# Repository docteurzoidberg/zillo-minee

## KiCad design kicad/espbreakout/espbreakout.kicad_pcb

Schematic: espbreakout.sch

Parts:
D1: POWER; LED_1206_3216Metric_Pad1.42x1.75mm_HandSolder
D2: RELAY; LED_1206_3216Metric_Pad1.42x1.75mm_HandSolder
H1, H2, H3, H4: MountingHole_Pad; MountingHole_3.2mm_M3_Pad_Via
J1: TEMPERATURE; PhoenixContact_MCV-G_03x3.81mm_Vertical
J2: LED DATA; PhoenixContact_MCV-G_03x3.81mm_Vertical
J3: UNK; PhoenixContact_MCV-G_03x3.81mm_Vertical
J4: POWER; PhoenixContact_MCV-G_03x3.81mm_Vertical
J5: CURRENT; PhoenixContact_MCV-G_03x3.81mm_Vertical
J6: RELAY; PhoenixContact_MCV-G_03x3.81mm_Vertical
J7: GROVE_I2C; JST_PH_S5B-PH-K_05x2.00mm_Angled
J8: SERIAL; Pin_Header_Straight_1x05_Pitch2.54mm
JP1, JP2: PLJP; SolderJumper-2_P1.3mm_Open_RoundedPad1.0x1.5mm
JP3, JP5, JP14: SolderJumper_2_Open; SolderJumper-2_P1.3mm_Open_TrianglePad1.0x1.5mm
JP4, JP6, JP7: D; SolderJumper-2_P1.3mm_Open_TrianglePad1.0x1.5mm
JP8, JP9, JP10, JP11, JP12, JP13: Jumper_3_Open; SolderJumper-3_P1.3mm_Open_Pad1.0x1.5mm
R1, R2: 4.7K; R_0805_HandSoldering
R3: 150; R_0805_HandSoldering
R4: 51; R_0805_HandSoldering
U1: ESP32-38pins; esp32 38pin azdelivery

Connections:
3V3: J7.3, J8.1, JP8.3, JP9.3, JP10.3, JP11.3, JP12.3, JP13.3, R1.1, R2.1, U1.1
5V: J7.1, JP1.2 (B), JP8.1, JP9.1, JP10.1, JP11.1, JP12.1, JP13.1, U1.19
CURRENT_SENSOR: JP6.1 (A)
GND: D1.1 (K), D2.1 (K), H1.1, H2.1, H3.1, H4.1, J1.3, J2.3, J3.3, J4.3, J5.3, J6.3, J7.2, J8.5, U1.14, U1.20, U1.26
GPIO0: J8.4, U1.33
LEDMATRIX: U1.9
LED_DATA: JP5.2 (B)
unnamed: D1.2 (A), R3.2
unnamed: D2.2 (A), R4.2
unnamed: J1.1, JP8.2
unnamed: J1.2, JP3.1 (A)
unnamed: J2.1, JP11.2
unnamed: J2.2, JP5.1 (A)
unnamed: J3.1, JP13.2
unnamed: J3.2, JP14.1 (A)
unnamed: J4.1, JP9.2
unnamed: J4.2, JP4.2 (B)
unnamed: J5.1, JP10.2
unnamed: J5.2, JP6.2 (B)
unnamed: J6.1, JP12.2
unnamed: J6.2, JP7.2 (B)
unnamed: JP1.1 (A), R3.1
unnamed: JP2.1 (A), R4.1
RELAY_TRIGGER: JP2.2 (B), JP7.1 (A)
RX: J8.3
SCL: J7.5, R2.2, U1.22
SDA: J7.4, R1.2, U1.25
TEMP_SENSOR: JP3.2 (B)
TX: J8.2

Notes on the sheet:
LED SIDE
POWER SIDE
PULLUPS
POWER NETS
LEDS

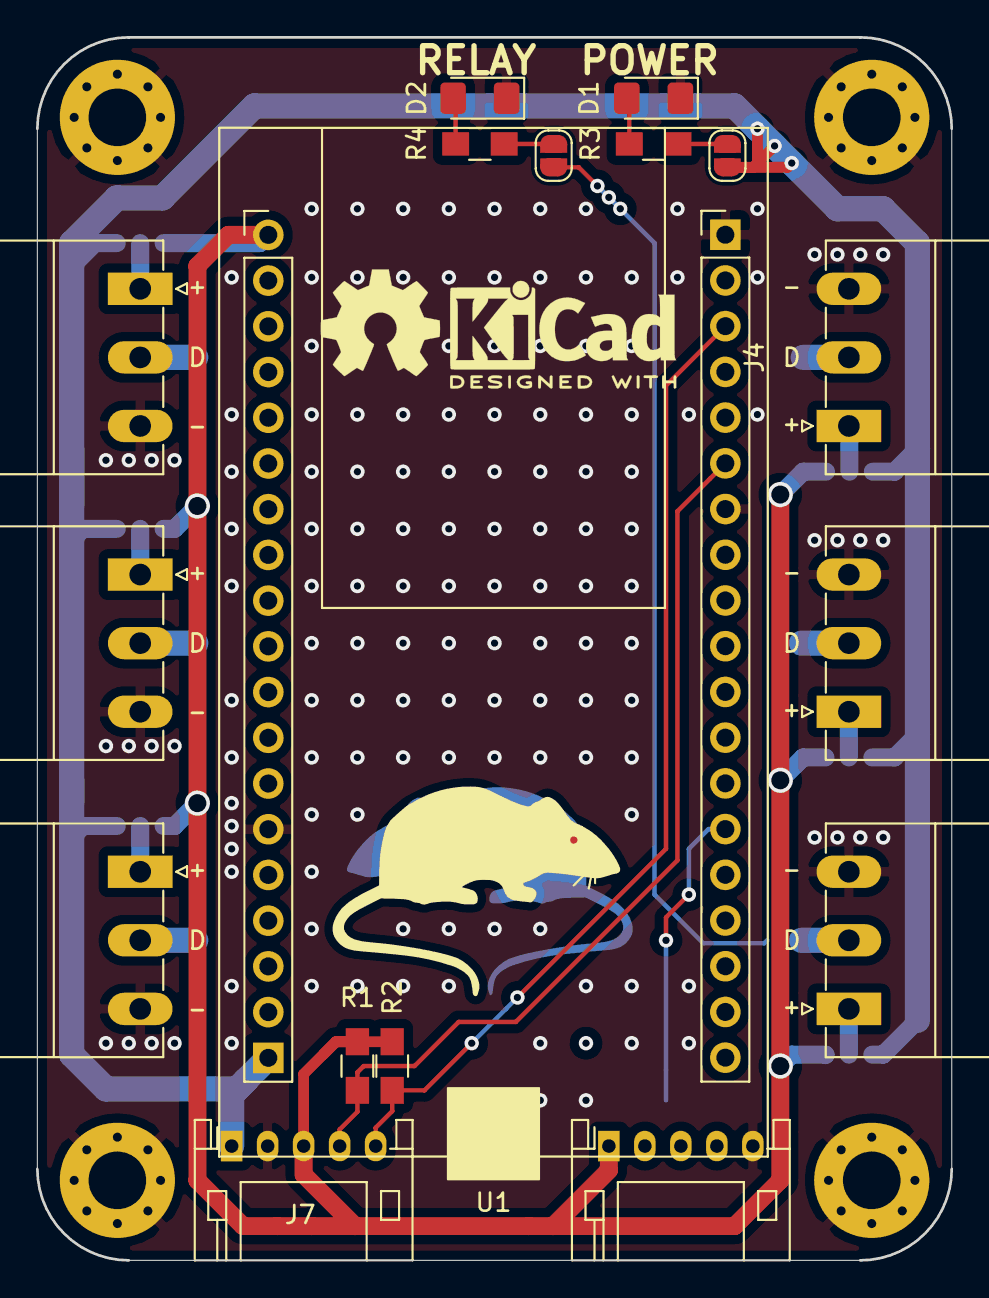
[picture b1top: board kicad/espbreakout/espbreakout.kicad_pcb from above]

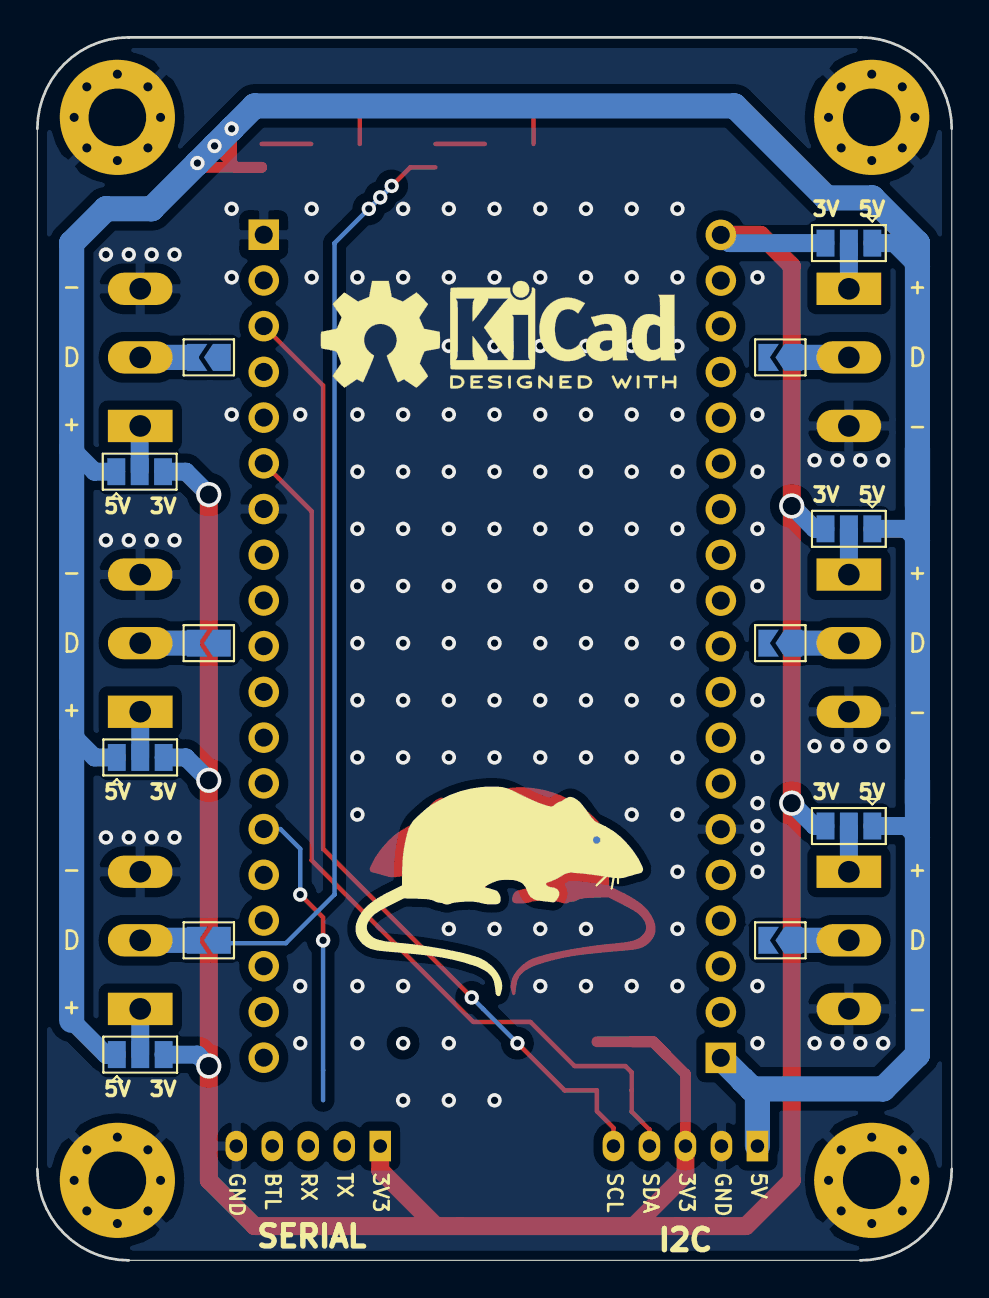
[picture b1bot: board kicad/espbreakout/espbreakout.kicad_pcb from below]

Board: 2 copper layers, 50.8 x 67.9 mm, 33 parts (12 on the bottom side), 23 nets.

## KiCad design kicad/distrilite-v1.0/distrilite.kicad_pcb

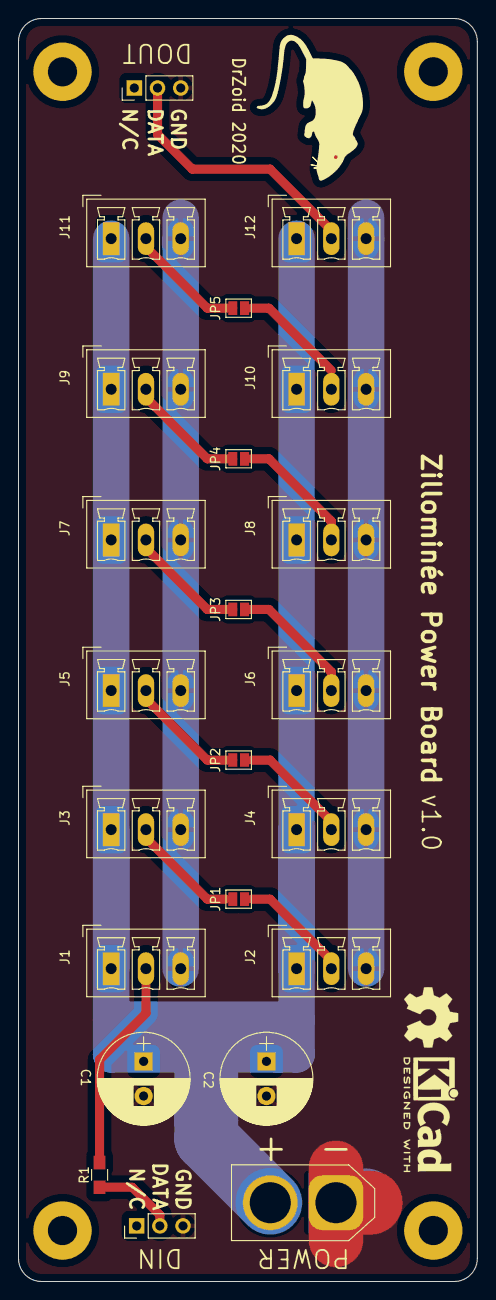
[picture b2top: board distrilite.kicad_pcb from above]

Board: 2 copper layers, 50.3 x 138.4 mm, 27 parts (0 on the bottom side), 15 nets.

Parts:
C1, C2: CP; CP_Radial_D10.0mm_P3.80mm
H1, H2, H3, H4: MountingHole; MountingHole_3.2mm_M3_Pad
J1, J2, J3, J4, J5, J6, J7, J8, J9, J10, J11, J12: Conn_01x03_Male; PhoenixContact_MCV-G_03x3.81mm_Vertical
J13: LED_DOUT; Pin_Header_Straight_1x03_Pitch2.54mm
J34: LED_DIN; Pin_Header_Straight_1x03_Pitch2.54mm
JP1, JP2, JP3, JP4, JP5: SolderJumper_2_Open; SolderJumper-2_P1.3mm_Open_Pad1.0x1.5mm
POWER1: XT60; AMASS_XT60-F_1x02_P7.20mm_Vertical
R1: 470; R_0805_HandSoldering

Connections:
+12V: C1.1, C2.1, J1.1, J2.1, J3.1, J4.1, J5.1, J6.1, J7.1, J8.1, J9.1, J10.1, J11.1, J12.1, POWER1.2
DATA_IN: J1.2, R1.2
DATA_OUT: J12.2, J13.2
GND: C1.2, C2.2, J1.3, J2.3, J3.3, J4.3, J5.3, J6.3, J7.3, J8.3, J9.3, J10.3, J11.3, J12.3, J13.3, J34.3, POWER1.1
unnamed: J2.2, JP1.1
unnamed: J3.2, JP1.2
unnamed: J4.2, JP2.1
unnamed: J5.2, JP2.2
unnamed: J6.2, JP3.1
unnamed: J7.2, JP3.2
unnamed: J8.2, JP4.1
unnamed: J9.2, JP4.2
unnamed: J10.2, JP5.1
unnamed: J11.2, JP5.2
unnamed: J34.2, R1.1

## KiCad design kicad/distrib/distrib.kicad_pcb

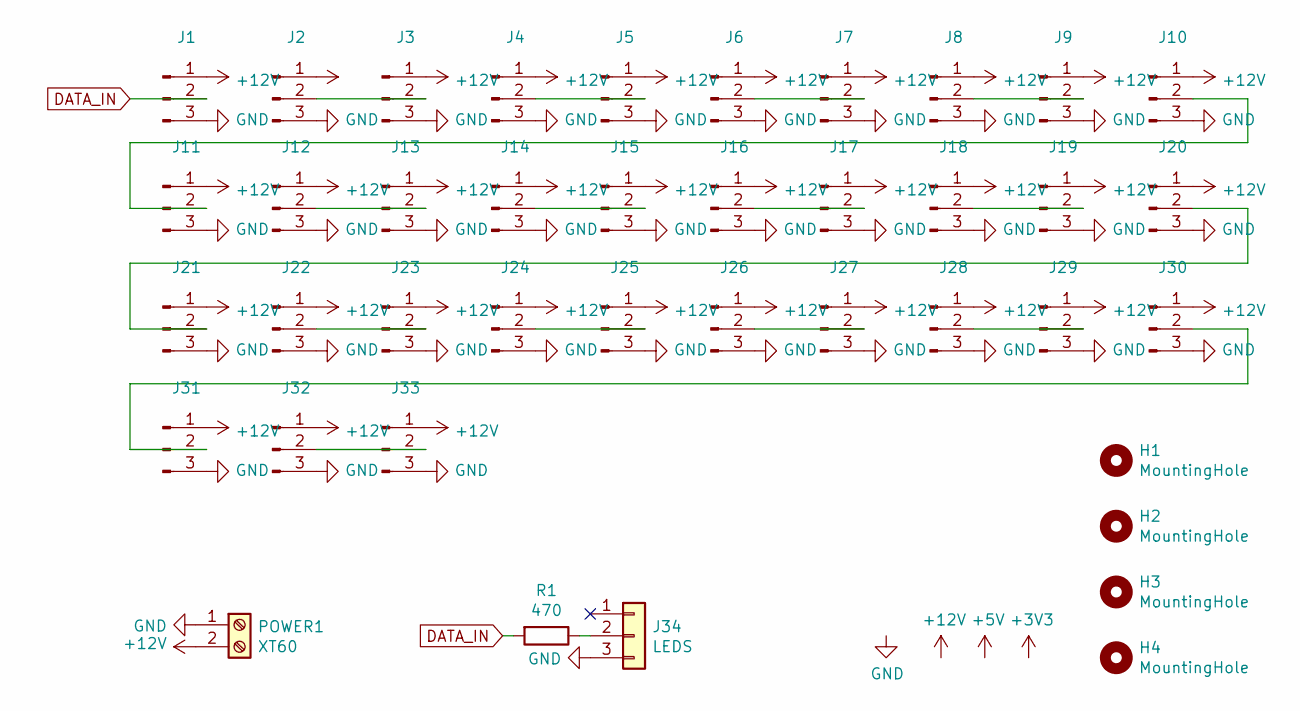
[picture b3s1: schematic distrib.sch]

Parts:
H1, H2, H3, H4: MountingHole; MountingHole_3.2mm_M3
J1, J2, J3, J4, J5, J6, J7, J8, J9, J10, J11, J12, J13, J14, J15, J16, J17, J18, J19, J20, J21, J22, J23, J24, J25, J26, J27, J28, J29, J30, J31, J32, J33: Conn_01x03_Male; PhoenixContact_MCV-G_03x3.81mm_Vertical
J34: LEDS; Pin_Header_Straight_1x03_Pitch2.54mm
POWER1: XT60; AMASS_XT60-F_1x02_P7.20mm_Vertical
R1: 470; R_0805_HandSoldering

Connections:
+12V: J1.1, J2.1, J3.1, J4.1, J5.1, J6.1, J7.1, J8.1, J9.1, J10.1, J11.1, J12.1, J13.1, J14.1, J15.1, J16.1, J17.1, J18.1, J19.1, J20.1, J21.1, J22.1, J23.1, J24.1, J25.1, J26.1, J27.1, J28.1, J29.1, J30.1, J31.1, J32.1, J33.1, POWER1.2; also elsewhere on the board
DATA_IN: J1.2, R1.2
GND: J1.3, J2.3, J3.3, J4.3, J5.3, J6.3, J7.3, J8.3, J9.3, J10.3, J11.3, J12.3, J13.3, J14.3, J15.3, J16.3, J17.3, J18.3, J19.3, J20.3, J21.3, J22.3, J23.3, J24.3, J25.3, J26.3, J27.3, J28.3, J29.3, J30.3, J31.3, J32.3, J33.3, J34.3, POWER1.1; also elsewhere on the board
unnamed: J2.2, J3.2
unnamed: J4.2, J5.2
unnamed: J6.2, J7.2
unnamed: J8.2, J9.2
unnamed: J10.2, J11.2
unnamed: J12.2, J13.2
unnamed: J14.2, J15.2
unnamed: J16.2, J17.2
unnamed: J18.2, J19.2
unnamed: J20.2, J21.2
unnamed: J22.2, J23.2
unnamed: J24.2, J25.2
unnamed: J26.2, J27.2
unnamed: J28.2, J29.2
unnamed: J30.2, J31.2
unnamed: J32.2, J33.2
unnamed: J34.2, R1.1

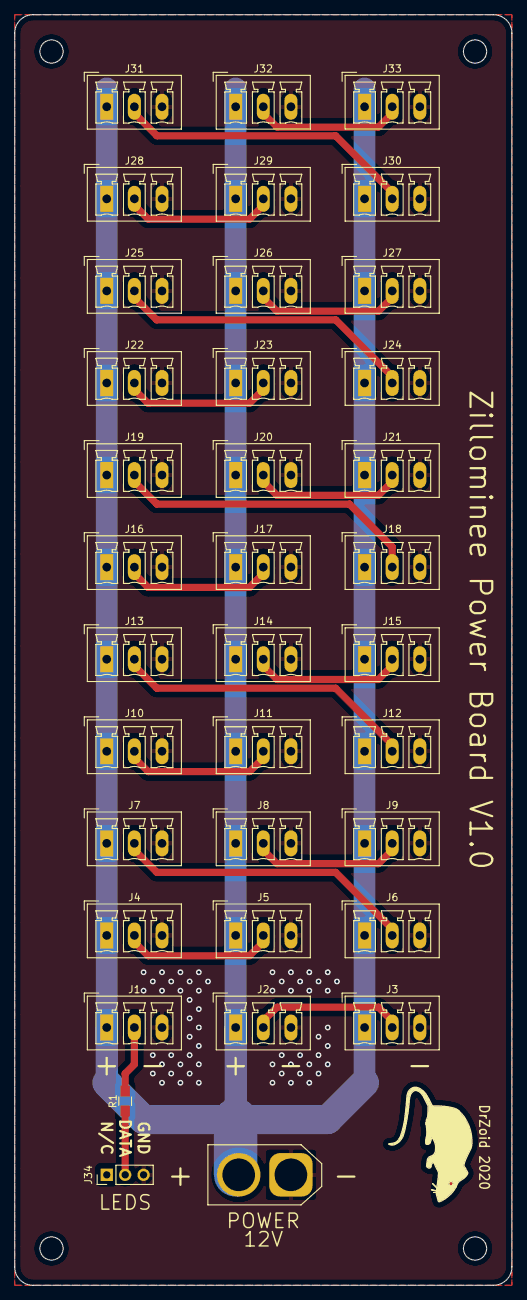
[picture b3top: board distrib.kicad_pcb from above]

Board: 2 copper layers, 68.6 x 175.3 mm, 40 parts (0 on the bottom side), 20 nets.

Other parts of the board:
POWER: XT60; AMASS_XT60-F_1x02_P7.20mm_Vertical

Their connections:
+12V: POWER.2; also elsewhere on the board
GND: POWER.1; also elsewhere on the board

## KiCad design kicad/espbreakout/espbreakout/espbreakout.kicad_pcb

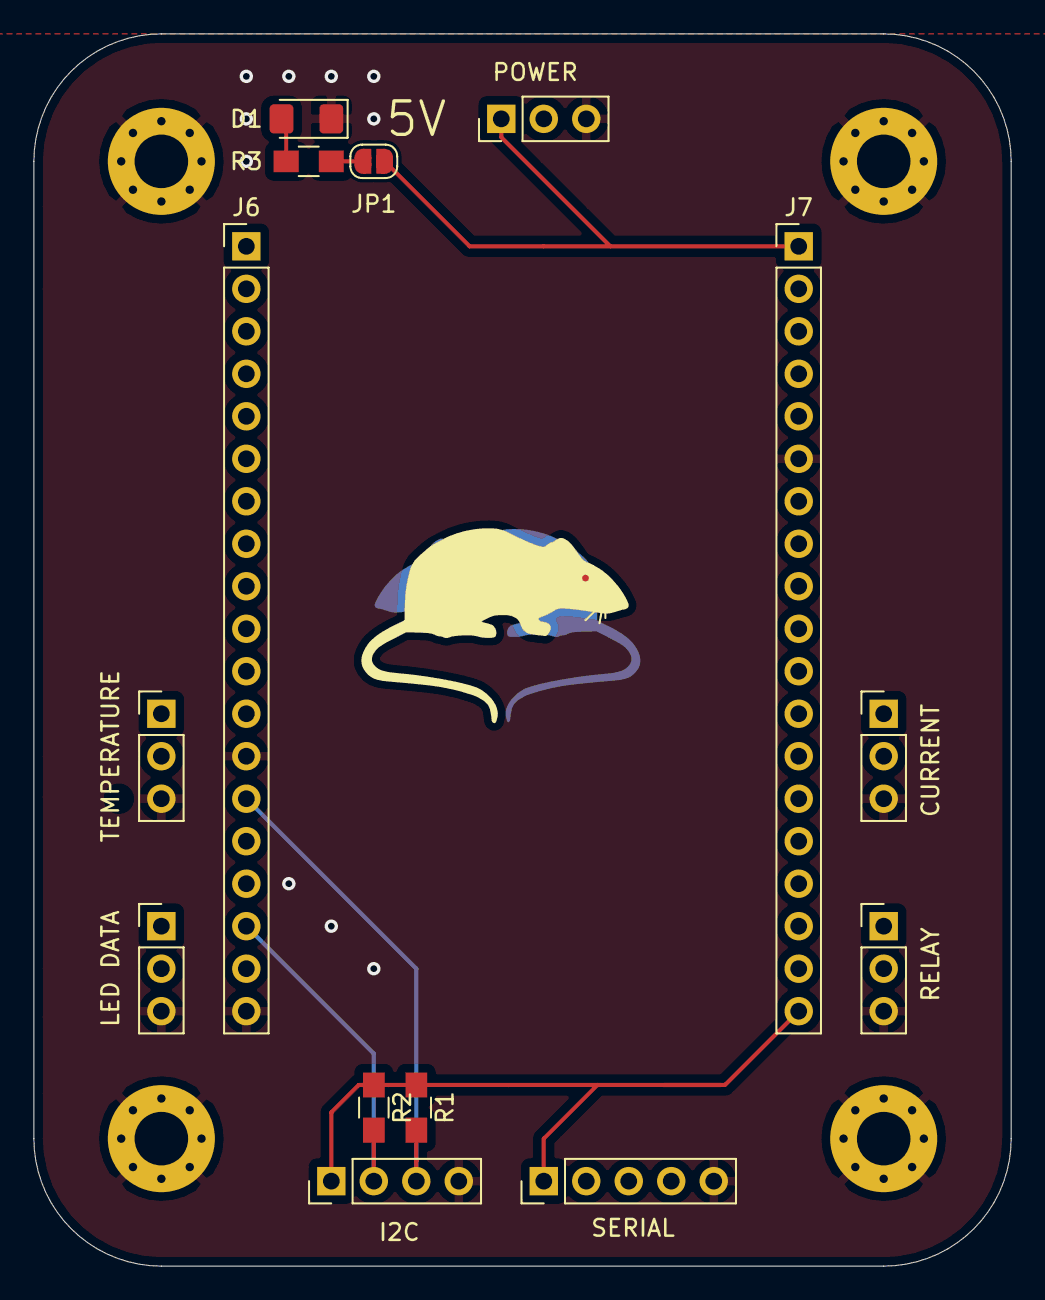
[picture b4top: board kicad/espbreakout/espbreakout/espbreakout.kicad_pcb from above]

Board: 2 copper layers, 58.4 x 73.7 mm, 18 parts (0 on the bottom side), 7 nets.

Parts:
D1: POWER; LED_1206_3216Metric_Pad1.42x1.75mm_HandSolder
H1, H2, H3, H4: MountingHole_Pad; MountingHole_3.2mm_M3_Pad_Via
J1: TEMPERATURE; Pin_Header_Straight_1x03_Pitch2.54mm
J2: POWER; Pin_Header_Straight_1x03_Pitch2.54mm
J3: CURRENT; Pin_Header_Straight_1x03_Pitch2.54mm
J4: LED DATA; Pin_Header_Straight_1x03_Pitch2.54mm
J5: RELAY; Pin_Header_Straight_1x03_Pitch2.54mm
J6, J7: Conn_01x19; Pin_Header_Straight_1x19_Pitch2.54mm
J8: I2C; Pin_Header_Straight_1x04_Pitch2.54mm
J9: SERIAL; Pin_Header_Straight_1x05_Pitch2.54mm
JP1: PLJP; SolderJumper-2_P1.3mm_Open_RoundedPad1.0x1.5mm
R1, R2: 4.7K; R_0805_HandSoldering
R3: 330; R_0805_HandSoldering

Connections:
3V3: J7.19, J8.1, J9.1, R1.1, R2.1
5V: J2.1, J7.1, JP1.2
GND: D1.1, H1.1, H2.1, H3.1, H4.1, J1.3, J2.3, J3.3, J4.3, J5.3, J6.13, J6.19, J7.6, J8.4, J9.5
unnamed: D1.2, R3.2
unnamed: JP1.1, R3.1
SCL: J6.17, J8.2, R2.2
SDA: J6.14, J8.3, R1.2

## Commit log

2020-10-01 distrib first
2020-10-01 autosave
2020-10-03 breakout
2020-10-04 distrib: ajout connecteur leds
2020-10-19 distrib board lite (x3)
2020-10-19 ajout condo et validation ?
2020-10-19 clearance et pad gnd
2020-10-19 gerbers
2020-10-19 JLCPCB -> archivage v1.0
2020-10-19 espbreakout move
2020-10-19 esp breakout board (wip)
2020-11-28 esp breakout
